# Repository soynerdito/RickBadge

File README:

# Badge for comunity inspired in Rick from Rick and Morthy.
PCB created with KiCad.

Circuit consists of an Attiny13A-SU and a shift register 74164 8 bit serial to parallel shift register.
The circuit includes a batter holder for a CR2032 battery.
Circuit also has 8 Leds.

As the moment of pushing repository circuit has never been tested.

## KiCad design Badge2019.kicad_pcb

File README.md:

# Badge for comunity inspired in Rick from Rick and Morthy.
PCB created with KiCad.

Circuit consists of an Attiny13A-SU and a shift register 74164 8 bit serial to parallel shift register.
The circuit includes a batter holder for a CR2032 battery.
Circuit also has 8 Leds.

As the moment of pushing repository circuit has never been tested.

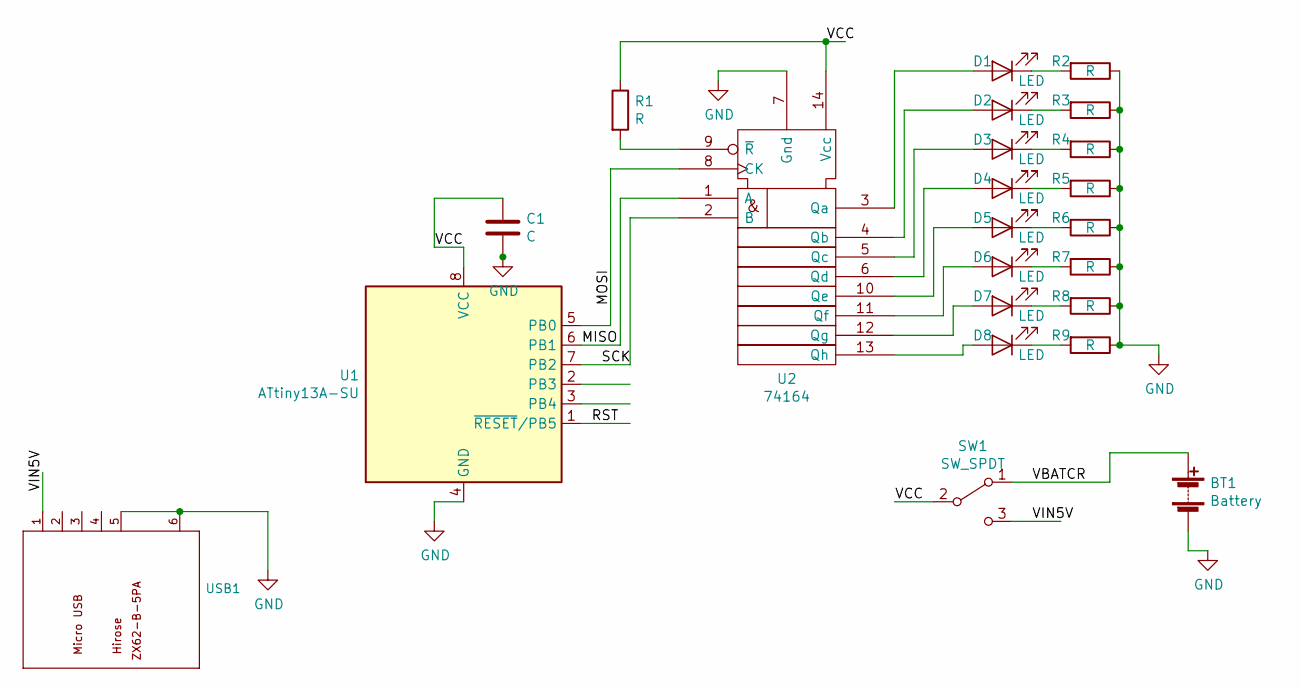
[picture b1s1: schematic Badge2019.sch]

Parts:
BT1: Battery; Keystone_103_1x20mm-CoinCell
C1: C; C_0603_HandSoldering
D1, D2, D3, D4, D5, D6, D7, D8: LED; LED_0603
R1, R2, R3, R4, R5, R6, R7, R8, R9: R; R0603
SW1: SW_SPDT; SW_SPDT_PCM12
U1: ATtiny13A-SU; SOIC-8-N
U2: 74164; SOIC-14_N
USB1: MICRO-USB-SMD_ZX62-B-5PA_; MICRO-USB5+6P-SMD-0.65-AB; MPN ZX62-B-5PA

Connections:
/MISO: U1.6 (PB1), U2.1 (A)
/MOSI: U1.5 (PB0), U2.8 (CK)
/RST: U1.1 (~RESET~/PB5)
/SCK: U1.7 (PB2), U2.2 (B)
/VBATCR: BT1.1 (+), SW1.1 (A)
/VCC: C1.1, R1.1, SW1.2 (B), U1.8 (VCC), U2.14 (Vcc)
/VIN5V: SW1.3 (C), USB1.1 (VBUS)
GND: BT1.2 (-), C1.2, R2.1, R3.1, R4.1, R5.1, R6.1, R7.1, R8.1, R9.1, U1.4 (GND), U2.7 (Gnd), USB1.5 (GND), USB1.6 (SHIELD), USB1.7 (SHIELD), USB1.8 (SHIELD), USB1.9 (SHIELD)
unnamed: D1.1 (K), R2.2
unnamed: D1.2 (A), U2.3 (Qa)
unnamed: D2.1 (K), R3.2
unnamed: D2.2 (A), U2.4 (Qb)
unnamed: D3.1 (K), R4.2
unnamed: D3.2 (A), U2.5 (Qc)
unnamed: D4.1 (K), R5.2
unnamed: D4.2 (A), U2.6 (Qd)
unnamed: D5.1 (K), R6.2
unnamed: D5.2 (A), U2.10 (Qe)
unnamed: D6.1 (K), R7.2
unnamed: D6.2 (A), U2.11 (Qf)
unnamed: D7.1 (K), R8.2
unnamed: D7.2 (A), U2.12 (Qg)
unnamed: D8.1 (K), R9.2
unnamed: D8.2 (A), U2.13 (Qh)
unnamed: R1.2, U2.9 (~R)

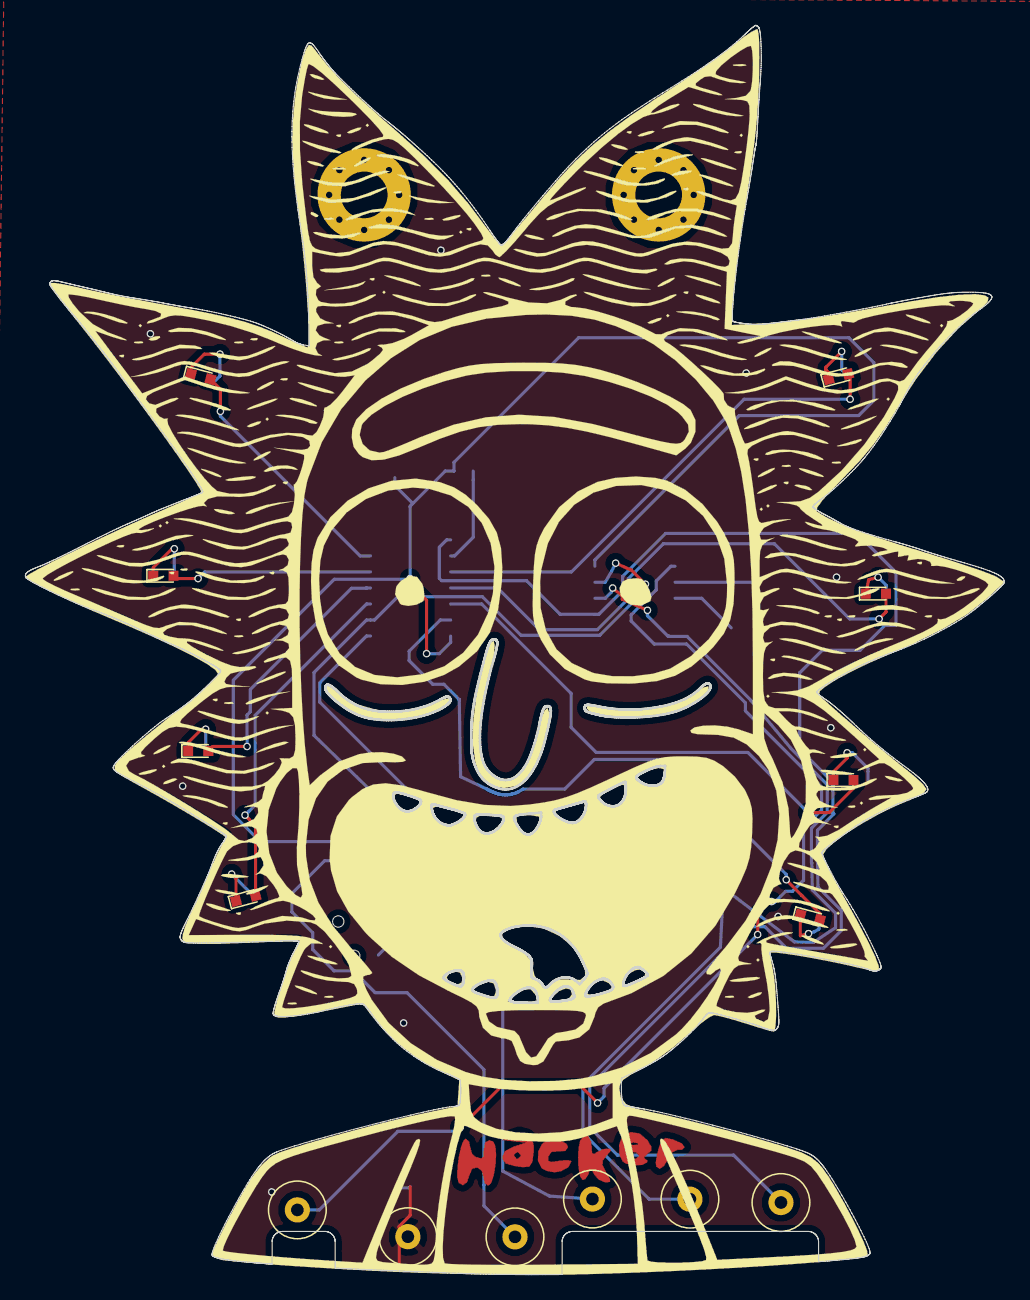
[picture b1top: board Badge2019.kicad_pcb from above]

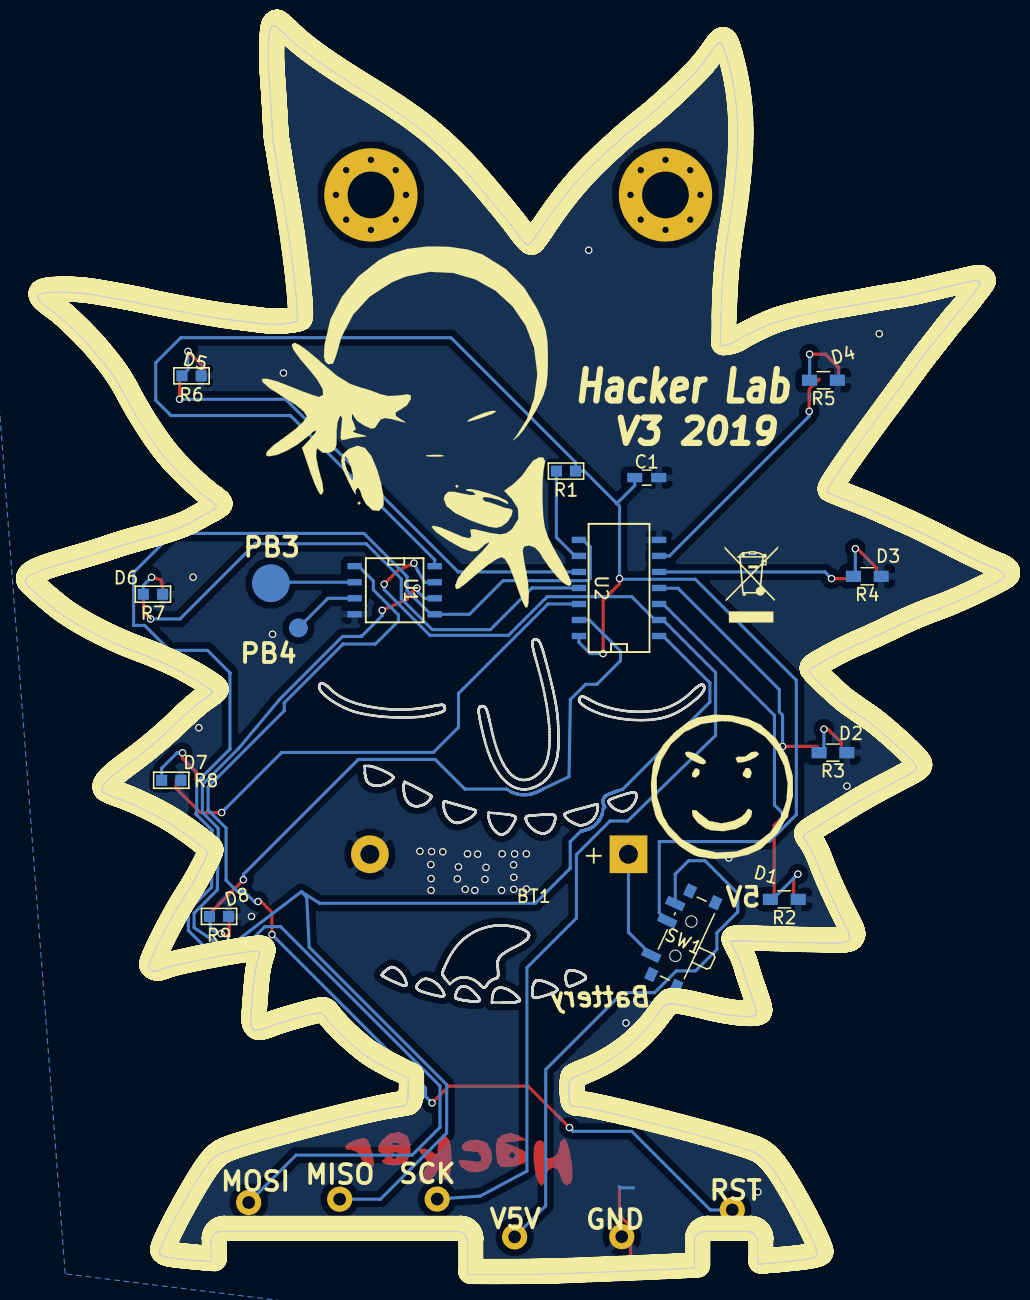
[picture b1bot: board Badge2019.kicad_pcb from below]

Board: 2 copper layers, 77.6 x 99.0 mm, 22 parts (14 on the bottom side), 23 nets.

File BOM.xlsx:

Designator | MPN/Seeed SKU | Qty | Link
D1,D2,D3,D4,D5,D6,D7,D8 | 304090043 | 8
R1,R2,R3,R4,R5,R6,R7,R8,R9 | RTT031500FTP | 9
USB1 | 320010005 | 1

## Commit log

2019-03-20 Adding readme
2019-03-20 updating render image
2019-05-01 Actual version send for mass production
2019-05-03 Moved border contacts to be inside the board. created files for jlpcb
2019-06-07 First try to make documentation
2019-06-07 moving stuff arround
2019-06-07 Adding already created images
2019-06-07 moving stuff arrround, fail and error/ retry
2019-06-07 just moving stuff retry
2019-06-07 correcting hyperlinks
2019-06-07 more links... well just one
2019-06-07 Adding BOM
2019-06-08 Updating documentation to add programming links
2019-06-08 Updating help site title
2019-06-23 Adding Presentation from keynote
2019-06-23 Updating documentation
